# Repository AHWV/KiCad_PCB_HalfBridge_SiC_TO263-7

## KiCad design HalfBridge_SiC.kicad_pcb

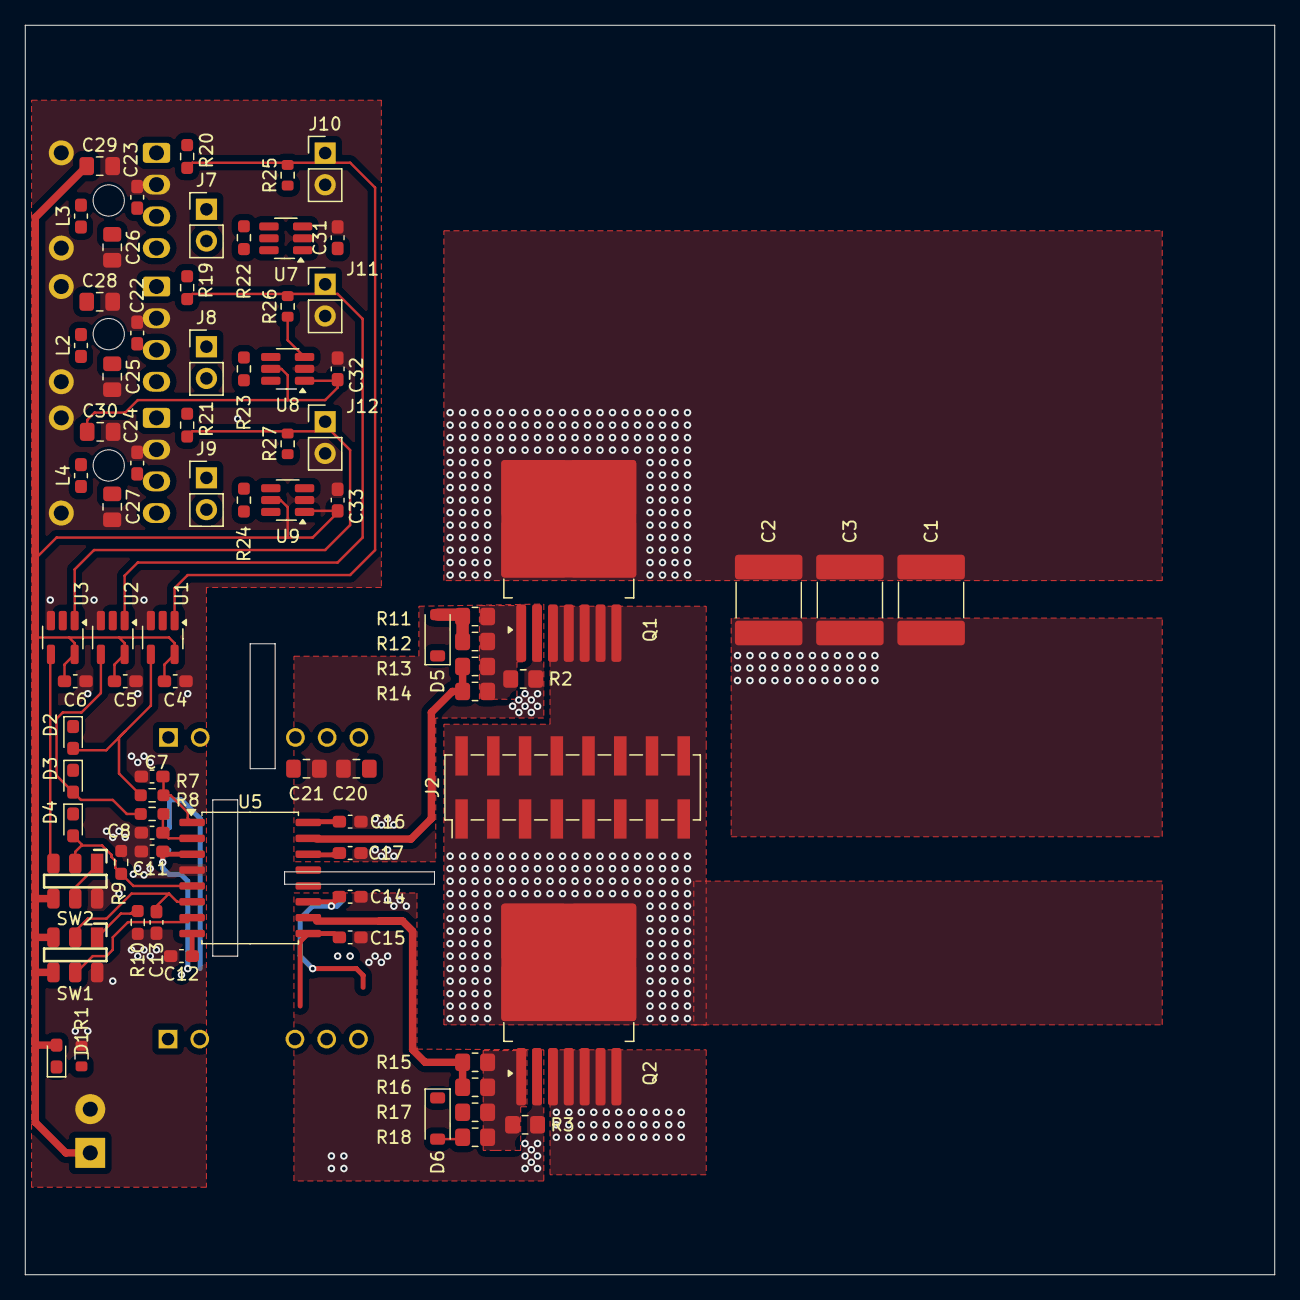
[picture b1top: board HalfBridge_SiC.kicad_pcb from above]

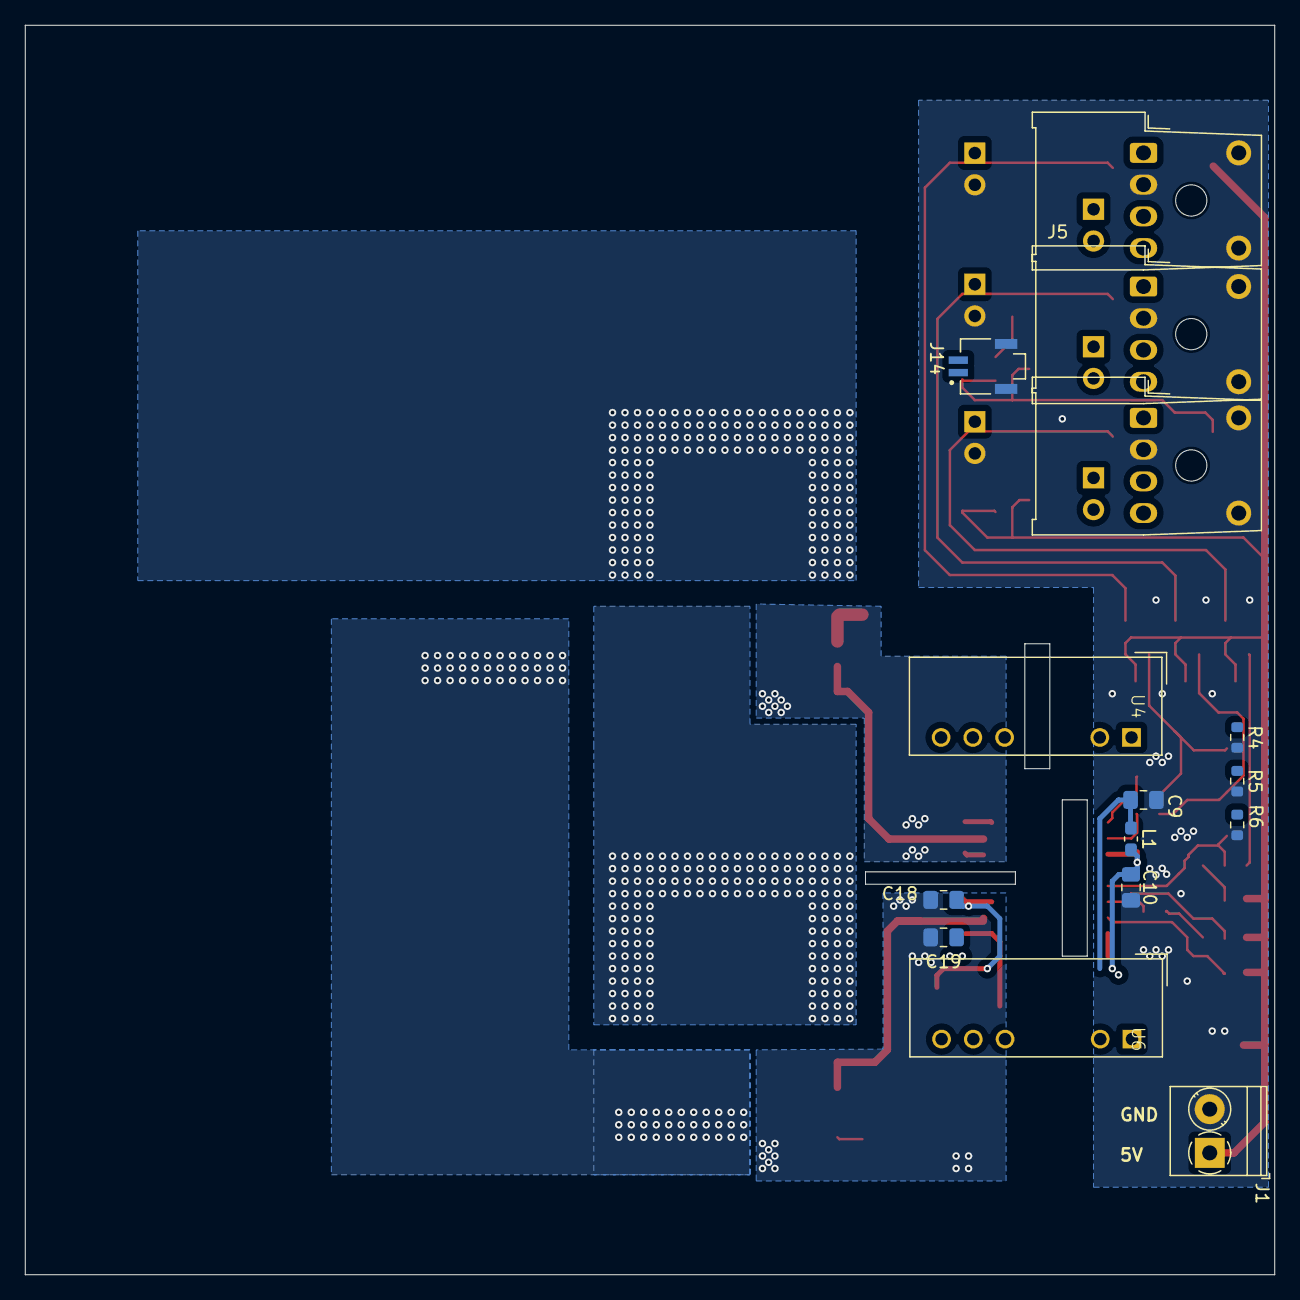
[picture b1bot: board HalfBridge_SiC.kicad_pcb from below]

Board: 2 copper layers, 100.0 x 100.0 mm, 95 parts (15 on the bottom side), 50 nets.

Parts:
C1, C2, C3: C; C_2220_5750Metric_Pad1.97x5.40mm_HandSolder
C4, C5, C6, C11, C12, C16, C17, C31, C32, C33: 100n; C_0603_1608Metric_Pad1.08x0.95mm_HandSolder
C7, C8, C13, C14, C15, C22, C23, C24: C; C_0603_1608Metric_Pad1.08x0.95mm_HandSolder
C9, C10, C18, C19, C20, C21, C25, C26, C27, C28, C29, C30: C; C_0805_2012Metric_Pad1.18x1.45mm_HandSolder
D1, D2, D3, D4: LED; LED_0603_1608Metric_Pad1.05x0.95mm_HandSolder
D5, D6: D_Schottky; D_SOD-123
J1: Screw_Terminal_01x02; TerminalBlock_Phoenix_PT-1,5-2-3.5-H_1x02_P3.50mm_Horizontal
J2: Conn_02x08_Odd_Even; PinHeader_2x08_P2.54mm_Vertical_SMD
J3, J4, J5: AFBR-2624Z; Broadcom_AFBR-16xxZ_Vertical
J7, J8, J9, J10, J11, J12: Conn_01x02; PinHeader_1x02_P2.54mm_Vertical
J14: Conn_01x02_Shielded; SAMTEC_T1M-02-F-SH-L-K
L1, L2, L3, L4: L; L_0603_1608Metric_Pad1.05x0.95mm_HandSolder
Q1, Q2: C3M0075120J; TO-263-7_TabPin8
R1, R4, R5, R6, R25, R26, R27: R; R_0603_1608Metric
R2, R3, R11, R12, R13, R14, R15, R16, R17, R18: R; R_0805_2012Metric_Pad1.20x1.40mm_HandSolder
R7, R8, R9, R10, R19, R20, R21, R22, R23, R24: R; R_0603_1608Metric_Pad0.98x0.95mm_HandSolder
SW1, SW2: CAS-D20X1; Nidec_Copal_CAS-D20A1
U1, U2, U3: 74AHC1G86; SOT-23-5_HandSoldering
U4, U6: RKD-052005D; Converter_DCDC_RECOM_RKZ-xx2005_Dual_THT_SIP7
U5: NCD57252; SOIC-16W_7.5x10.3mm_P1.27mm
U7, U8, U9: MAX3284E; SOT-23-6_Handsoldering

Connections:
/HalfBridge_Diff/gnd: C4.2, C5.2, C6.2, C7.2, C8.2, C9.2, C10.2, C11.2, C12.2, C13.2, C22.2, C23.2, C24.2, C25.2, C26.2, C27.2, C28.2, C29.2, C30.2, C31.2, C32.2, C33.2, J1.2, J3.2 (VEER), J3.5 (HP), J3.8 (HP), J4.2 (VEER), J4.5 (HP), J4.8 (HP), J5.2 (VEER), J5.5 (HP), J5.8 (HP), J10.2, J11.2, J12.2, J14.SH (Shield), R1.2, R4.2, R5.2, R6.2, R9.2, R10.1, SW1.4 (A), SW2.4 (A), U1.3 (GND), U2.3 (GND), U3.3 (GND), U5.4 (GND), U7.2 (GND), U8.2 (GND), U9.2 (GND)
/HalfBridge_Diff/ina_d: J10.1, R20.1, R25.2, U1.1
/HalfBridge_Diff/ina_da: J7.2, R22.1, U7.6 (A)
/HalfBridge_Diff/ina_db: J7.1, R22.2, U7.4 (B)
/HalfBridge_Diff/ina_nd: R25.1, U7.3 (RO)
/HalfBridge_Diff/inb_d: J11.1, R19.1, R26.2, U2.1
/HalfBridge_Diff/inb_da: J8.2, J14.1, R23.1, U8.6 (A)
/HalfBridge_Diff/inb_db: J8.1, J14.2, R23.2, U8.4 (B)
/HalfBridge_Diff/inb_nd: R26.1, U8.3 (RO)
/HalfBridge_Diff/inen_d: J12.1, R21.1, R27.2, U3.1
/HalfBridge_Diff/inen_da: J9.2, R24.1, U9.6 (A)
/HalfBridge_Diff/inen_db: J9.1, R24.2, U9.4 (B)
/HalfBridge_Diff/inen_nd: R27.1, U9.3 (RO)
/HalfBridge_Diff/vcc: C4.1, C5.1, C6.1, C9.1, C28.1, C29.1, C30.1, C31.1, C32.1, C33.1, D1.2 (A), J1.1, L1.1, L2.2, L3.2, L4.2, SW1.3 (C), SW1.6 (C), SW2.6 (C), U1.5 (VCC), U2.5 (VCC), U3.5 (VCC), U7.1 (VCC), U7.5 (VL), U8.1 (VCC), U8.5 (VL), U9.1 (VCC), U9.5 (VL)
/HalfBridge_GateDriver/anb: SW1.5 (B), U5.7 (ANB)
/HalfBridge_GateDriver/asgh: D5.2 (A), R11.1, R12.1
/HalfBridge_GateDriver/asgl: D6.2 (A), R17.1, R18.1
/HalfBridge_GateDriver/dis: D4.2 (A), R9.1, SW2.2 (B), U5.5 (DIS)
/HalfBridge_GateDriver/dis_i: SW2.1 (A), SW2.5 (B)
/HalfBridge_GateDriver/dis_x: SW2.3 (C), U3.4
/HalfBridge_GateDriver/dt: C13.1, SW1.2 (B), U5.6 (DT)
/HalfBridge_GateDriver/gonh: D5.1 (K), R13.1, R14.1, U5.15 (OUTA)
/HalfBridge_GateDriver/gonl: D6.1 (K), R15.1, R16.1, U5.10 (OUTB)
/HalfBridge_GateDriver/inaf: C7.1, R7.2, U5.1 (INA)
/HalfBridge_GateDriver/inbf: C8.1, R8.2, U5.2 (INB)
/HalfBridge_GateDriver/inga: D2.2 (A), R7.1, U1.4
/HalfBridge_GateDriver/ingb: D3.2 (A), R8.1, U2.4
/HalfBridge_GateDriver/kh: C16.2, C17.1, C20.2, C21.1, Q1.2 (DS), R2.2
/HalfBridge_GateDriver/kl: C14.2, C15.1, C18.2, C19.1, Q2.2 (DS), R3.2
/HalfBridge_GateDriver/rdt: R10.2, SW1.1 (A)
/HalfBridge_GateDriver/vcci: C10.1, C11.1, C12.1, L1.2, U5.3 (VCCI), U5.8 (VCCI)
/HalfBridge_GateDriver/vddh: C16.1, C20.1, U4.7 (+VDC), U5.16 (VDDA)
/HalfBridge_GateDriver/vddl: C14.1, C18.1, U5.11 (VDDB), U6.7 (+VDC)
/HalfBridge_GateDriver/vssh: C17.2, C21.2, U4.5 (-VDC), U5.14 (VSSA)
/HalfBridge_GateDriver/vssl: C15.2, C19.2, U5.9 (VSSB), U6.5 (-VDC)
/HalfBridge_Optical/oina: J4.1 (Data_Out), R20.2
/HalfBridge_Optical/oinb: J3.1 (Data_Out), R19.2
/HalfBridge_Optical/oinen: J5.1 (Data_Out), R21.2
/HalfBridge_Optical/vcca: C23.1, C26.1, J4.3 (VCCR), L3.1
/HalfBridge_Optical/vccb: C22.1, C25.1, J3.3 (VCCR), L2.1
/HalfBridge_Optical/vccen: C24.1, C27.1, J5.3 (VCCR), L4.1
/HalfBridge_Power/dcn: C1.2, C2.2, C3.2, Q2.3 (S), Q2.4 (S), Q2.5 (S), Q2.6 (S), Q2.7 (S)
/HalfBridge_Power/dcp: C1.1, C2.1, C3.1, Q1.8 (D)
/HalfBridge_Power/gh: Q1.1 (G), R2.1, R11.2, R12.2, R13.2, R14.2
/HalfBridge_Power/gl: Q2.1 (G), R3.1, R15.2, R16.2, R17.2, R18.2
/HalfBridge_Power/ph: J2.1, J2.2, J2.3, J2.4, J2.5, J2.6, J2.7, J2.8, J2.9, J2.10, J2.11, J2.12, J2.13, J2.14, J2.15, J2.16, Q1.3 (S), Q1.4 (S), Q1.5 (S), Q1.6 (S), Q1.7 (S), Q2.8 (D)
unnamed: D1.1 (K), R1.1
unnamed: D2.1 (K), R4.1
unnamed: D3.1 (K), R5.1
unnamed: D4.1 (K), R6.1

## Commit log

2024-08-20 gate driver
2024-08-26 symbol library gatedriver
2024-08-27 switch dpdt 3d model
2024-08-30 dc dc 3d
2024-09-02 position
2024-09-02 diff rx
2024-09-03 quad diff receiver
2024-09-11 not gate
2024-09-12 new optical diff xor
2024-09-23 diff circuit
2024-09-25 pcb position
2024-10-09 route
2024-10-11 horizontal connector
2024-10-16 ruler heatsink
